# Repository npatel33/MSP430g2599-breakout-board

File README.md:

# MSP430g2955-breakout-board
MSP430G2955 TSSOP-38 to DIP breakout board

Breakout board is designed in Open-source PCB CAD Software KiCAD.

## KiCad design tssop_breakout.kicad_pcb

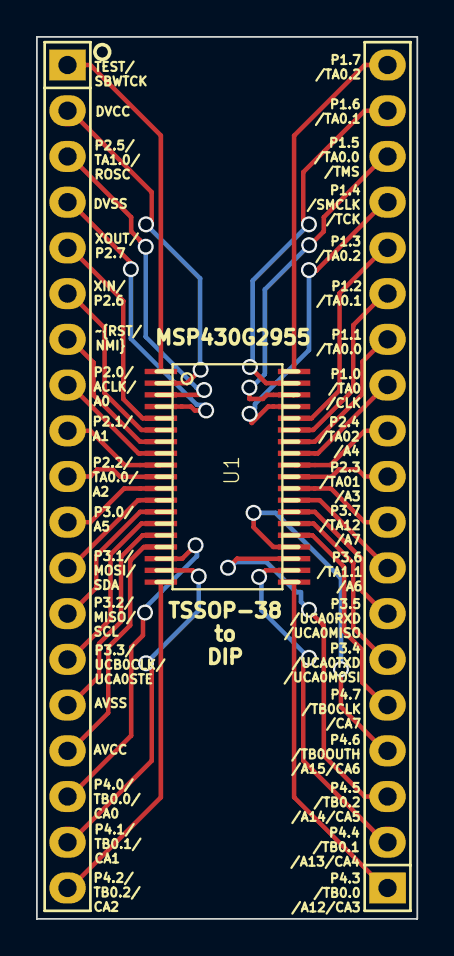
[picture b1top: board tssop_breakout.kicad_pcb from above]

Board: 2 copper layers, 21.1 x 49.0 mm, 3 parts (0 on the bottom side), 38 nets.

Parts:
P1, P2: CONN_01X19; Pin_Header_Straight_1x19
U1: MSP430G2955IDA38; AB2_TSSOP38_W

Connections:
/1: P1.1, U1.1
/2: P1.2, U1.2
/3: P1.3, U1.3
/4: P1.4, U1.4
/5: P1.5, U1.5
/6: P1.6, U1.6
/7: P1.7, U1.7
/8: P1.8, U1.8
/9: P1.9, U1.9
/10: P1.10, U1.10
/11: P1.11, U1.11
/12: P1.12, U1.12
/13: P1.13, U1.13
/14: P1.14, U1.14
/15: P1.15, U1.15
/16: P1.16, U1.16
/17: P1.17, U1.17
/18: P1.18, U1.18
/19: P1.19, U1.19
/20: P2.1, U1.20
/21: P2.2, U1.21
/22: P2.3, U1.22
/23: P2.4, U1.23
/24: P2.5, U1.24
/25: P2.6, U1.25
/26: P2.7, U1.26
/27: P2.8, U1.27
/28: P2.9, U1.28
/29: P2.10, U1.29
/30: P2.11, U1.30
/31: P2.12, U1.31
/32: P2.13, U1.32
/33: P2.14, U1.33
/34: P2.15, U1.34
/35: P2.16, U1.35
/36: P2.17, U1.36
/37: P2.18, U1.37
/38: P2.19, U1.38

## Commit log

2015-02-22 pcb files
2015-05-16 changed wrong footprint
2015-05-16 edited
